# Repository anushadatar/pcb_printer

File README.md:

# Etch a Schech : CNC PCB Mill
This repository contains documentation, firmware, and software for Aiden Carley-Clopton, Quinn Kelley, Josh Deng, and Anusha Datar's Olin College Principles of Engineering FA18 final project. Over the course of three two-week sprints, we developed a highly functional and robust two-axis compound table with z-axis spindle assembly capable of milling Printed Circuit Boards (PCBs).

## Docs
The docs directory contains the source for the project [website](https://anushadatar.github.io/pcb_printer/), which includes extensive documentation of the overall project architeture, subsystem development, and the design and implementation process. It also contains a more general [poster](https://github.com/anushadatar/pcb_printer/blob/master/docs/artifacts/poster.pdf) for external documentation purposes.

## Firmware
The firmware directory contains the production source code for the real-time control system of the final project and test code associated with hardware integration and system maintenance. 

The [gcode_parse/](https://github.com/anushadatar/pcb_printer/tree/master/firmware/gcode_parse) directory contains code that, with the necessary dependencies, can be compiled for the Arduino Uno V3 and flashed onto the chip by means of the [gcode_parse.ino](https://github.com/anushadatar/pcb_printer/blob/master/firmware/gcode_parse/gcode_parse.ino) file. 

## Software
The software directory contains the software to run the high-level computation necessary to determine and send commands to the real-time controller. 

## Dependencies
The [software page of the project website](https://anushadatar.github.io/pcb_printer/software.html) contains links to all of the external software packages necessary to run this code. For more software setup details for the computational platform, use the software [guide](https://github.com/anushadatar/pcb_printer/blob/master/software/README.md). Note that a new run file with the proper pathing is necessary for any new environment, and for the code to run properly the environment must be UNIX-compliant.

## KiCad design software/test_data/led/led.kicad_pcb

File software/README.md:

This software directory's function is to develop a framework to convert a .gbr
file output into a gcode equivalent file (containing coordinates and paths) and then convert that into
paths for the CNC. Those paths can then yield motor instructions for the CNC.

The main path planning is handled by the third-party tool Flatcam. Installation can be tricky; streamlined Ubuntu instructions
are included below. Raspberry Pi setup requires additional adjustments to the Flatam stack - contact us for details!

## Linux Setup Instructions
While the Etch A Schech uses a Raspberry Pi to setup up computation and streaming, it can often be more convenient to use a machine with Linux for software and testing. To set up this framework, first install the Flatcam Dependencies:
Some of the dependencies will need to be installed separately:
 - [SIP](https://www.riverbankcomputing.com/software/sip/download)
 
Download the newest stable source .tar.gz file from [here](https://www.riverbankcomputing.com/software/sip/download). Untar it using
`tar -xvf [folderName] `. 

Then, install the package with the following commands. 
~~~~~
cd [folderName]
python3 configure.py
make
sudo make install
~~~~~
- [PyQt4](https://www.riverbankcomputing.com/software/pyqt/download)

Download the newest stable source .tar.gz file from [here](https://www.riverbankcomputing.com/software/sip/download). Untar it using
`tar -xvf [folderName] `. 

Then, install the package with the following commands. If this fails, try moving on to the next step - it may be resolved by the Flatcam setup_ubuntu shell script.
~~~~~
cd [folderName]
python3 configure.py 
make
sudo make install
~~~~~
- [Flatcam 8.5](https://bitbucket.org/jpcgt/flatcam/downloads/) 

Finally, actually install flatcam. Grab the zip file for Flatcam from [here](https://bitbucket.org/jpcgt/flatcam/downloads/).
~~~~
cd [folderName]
chmod +x setup_ubuntu.sh
sudo ./setup_ubuntu.sh
python FlatCAM.py
~~~~
A flatcam window should launch following this final command. 

Once the proper software has been installed, configure the necessary environment variables to run the bash scripts.
To do that, instantiate pointers to this software folder and to your flatcam installation by adding the following lines to your .bashrc:
~~~~
export $ETCH_SW_DIR='/PATH/TO/SW/DIR'
export $FLATCAM_DIR='/PATH/TO/FLATCAM/INSTALL'
~~~~

This system has been validated on Ubuntu 16.04, Ubuntu 18.04, and Raspbian Jessie.

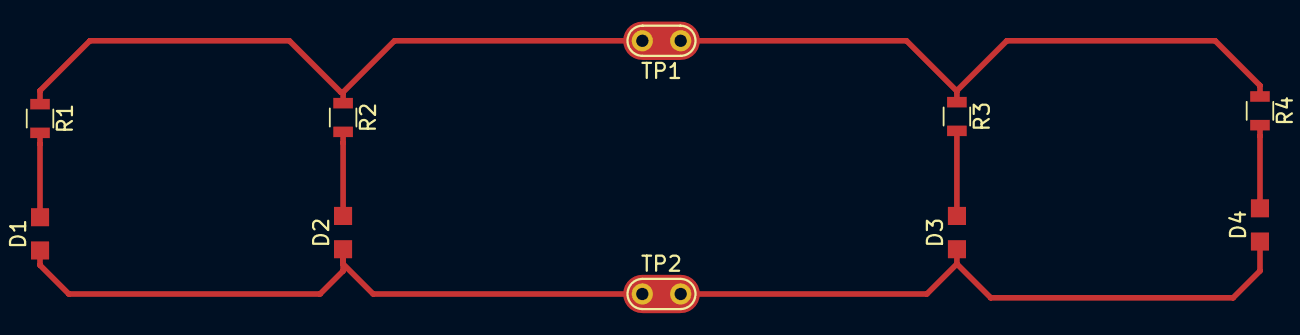
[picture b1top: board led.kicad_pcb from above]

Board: 2 copper layers, 10 parts (0 on the bottom side), 6 nets.

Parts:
D1, D2, D3, D4: LED; LED_0805_No_Silk_OEM
R1, R2, R3, R4: R; R_0805
TP1, TP2: TestPoint; Test_Point

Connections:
GND: D1.1, D2.1, D3.1, D4.1, TP2.1
unnamed: D1.2, R1.2
unnamed: D2.2, R2.2
unnamed: D3.2, R3.2
unnamed: D4.2, R4.2
unnamed: R1.1, R2.1, R3.1, R4.1, TP1.1

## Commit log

2018-10-15 add sample gerber files
2018-10-15 kicad 5 x2 example
2018-10-16 Reorg and architecture start.
2018-10-16 reorg
2018-10-17 stepper testing file and h bridge schematic project
2018-10-17 Reorganization.
2018-10-20 basic stepper functional
2018-10-23 started writing this buggy gcode parse lol
2018-10-23 more reorg
2018-10-23 add line drawing function
2018-10-23 fix stepper class motor rpm so that it compiles
2018-10-24 supposedly finished basic gcoder parse that reads XY and G
2018-10-24 Test two (2) steppers
2018-10-24 but on an arduino
2018-10-24 able to do rectangular drawing
2018-10-24 added start of arc
2018-10-24 too fast too furious
2018-10-24 basic flatcam gcode parser
2018-10-24 comment gcode_format.py
2018-10-25 x and y moves at the same time; add a space in front of gcoder formatting
2018-10-25 change cm_scaling so that the gantry thing draws circle
2018-10-26 default relative mode and remove the additional step in moving
2018-10-26 Starting cleanup
2018-10-28 Pushing raspi gcode test data.
2018-10-29 added a sample command line parser; started the streamer code; deleted serial config from format.py
2018-10-30 gcode streaming in relative x, y, z
2018-10-30 add finished gcode streamer coder; to be tested
2018-11-02 moved gcode parser
2018-11-02 added test scripts. Maybe set up an ubuntu testing environment.
2018-11-02 a script?
2018-11-04 modify gcode formatter to give the write dimension in mm and catch different combinations of X,Y,Z
2018-11-06 stepper speed to 60; encode all python streaming messages; line termination with \n and request for new line is $
2018-11-07 actually call the stream function; add dremel motor arduino code
2018-11-08 started function docs
2018-11-08 stream capability
2018-11-08 reorg for sprint 2 review prep
2018-11-08 don't run everything at once
2018-11-13 easy state machine then I guess?
2018-11-14 adding more automation stuff for raspi config.
2018-11-14 renamed one (1) folder
2018-11-14 Create CNAME
2018-11-16 started python script to generate tcl file.
2018-11-21 put up a template site, sad
2018-11-21 Create images
2018-11-21 Rename docs/README.md to docs/css/README.md
2018-11-21 starting config
2018-11-21 added more etch a schech words.
2018-11-21 removed bottom carosel and footer.
2018-11-21 added pages + nav
2018-11-22 Added page banners.
2018-11-22 added artifacts folder.
2018-11-23 Created script automation and added example stuff.
2018-11-24 Added SVG file support.
2018-11-24 Added differentiated run scripts.
2018-11-24 added the start of an explanation
2018-11-24 literally added a comment to pi_run. TODO check that it works.
2018-11-24 Update issue templates
2018-11-25 fix microstep connection error in software
2018-11-26 adding more state to allow arduino to control motor on/off
2018-11-27 updated README after setting up yet another pi
2018-11-27 click click svg
2018-11-28 decoder capability
2018-11-29 updated with encoder parsing
2018-11-29 z axis testing
2018-11-29 ino file changes.
2018-11-29 What is a GUI and who let it happen.
2018-11-29 update loaded to arduino
2018-11-29 adding doc for raspi setup things.
2018-11-29 fix z axis positioning
2018-11-29 change knob scaling factor
2018-11-29 we out here trying
2018-11-30 pcb traces
2018-11-30 added to josh's run script
2018-11-30 olin O
2018-11-30 updating with o gcode/
2018-12-01 proto board circuit
2018-12-02 update circuit to include separate power control for DC motor
2018-12-02 the whole gang's here folks
2018-12-02 we out here adding links
2018-12-02 fixed carousel
2018-12-03 update to make axis change circuit
2018-12-03 but who is quinn kelley?
2018-12-04 updated schematic with nfet driving the brushed motor
2018-12-04 we will try to drill holes
2018-12-04 jogging axes are now live
2018-12-06 Web design is my passion
2018-12-07 added placeholder images.
2018-12-07 adding circuit images
2018-12-07 Clicky photos
2018-12-07 change table name
2018-12-07 remove the black box around home
2018-12-07 adding some unformatted content to electrical, hope I didn't break anythign
2018-12-07 fixing budget site
2018-12-07 dumped some content into sprints; added unenclosed tags
2018-12-08 etch not ech
2018-12-08 L for testing
2018-12-08 ????????????? exit state.
2018-12-08 update website, add exit state for the printer
2018-12-08 gui updates. to port to pi, just change every instance of anusha to pi
2018-12-09 Pi run gui
2018-12-09 more words about power
2018-12-09 even more words
2018-12-09 Fixed some photos.
2018-12-09 please help
2018-12-09 stay centered, kids
2018-12-09 Fixed centering.
2018-12-09 final sprint...
2018-12-09 witty comments?
2018-12-09 fix wit a bit
2018-12-09 fix print 3 image naming
2018-12-10 limit switch code; update schematic; website wit fix
2018-12-10 1/123128382138
2018-12-10 new logo
2018-12-10 state machine for arduino
2018-12-10 change the scaling of electrical images from absolute to relative
2018-12-11 name tag
2018-12-11 drill
2018-12-11 kids just want to drill holes and draw pictures
2018-12-11 go away edges
2018-12-11 look at output.gcode
2018-12-11 L but larger
2018-12-11 L but positive
2018-12-11 Github messenger
2018-12-11 taking reasonably sized ls
2018-12-11 4th quadron L
2018-12-11 4th quadron l positive
2018-12-11 Please:
2018-12-11 round to 2 decimal places
2018-12-11 josh's stupidity fix
2018-12-12 write code for live z adjustment
2018-12-12 added gcode tests
2018-12-12 added mpst recent
2018-12-12 pi gui script no flash drive
2018-12-12 please work
2018-12-13 pushing for testing
2018-12-13 okay let's just ignore this
2018-12-13 stream
2018-12-13 i ate delays.
2018-12-13 asdaslkdjlsa
2018-12-13 smaller logo
2018-12-13 led output
2018-12-13 more info on the firmware stuff
2018-12-13 what worked
2018-12-13 logo update
2018-12-13 huge day to be a mechanical menu
2018-12-13 added some pages
2018-12-13 keep on pushing
2018-12-13 logo in italic
2018-12-13 added more standards and content.
2018-12-13 partial site
2018-12-13 added some to sprint pages...
2018-12-13 continued adding sprint docs..
2018-12-13 add abouts about streamer and formater
2018-12-13 Adding final zipped CAD
2018-12-13 link cad on index page
2018-12-13 clarity
2018-12-14 software adding dependencies
2018-12-14 break line
2018-12-14 HUGE gui guy
2018-12-14 Software description
2018-12-14 led doable
2018-12-14 just u wait
2018-12-14 overwriting process page
2018-12-14 Adding mechanical documentation changes
2018-12-14 we tryin
2018-12-14 Where we're going, we don't need goals.
2018-12-14 updating spindle and table pages
2018-12-14 compound table gang
2018-12-14 Updating mechanical overview page
2018-12-14 fixing navbar. not done yet.
2018-12-14 fixed navbars...
2018-12-14 all pain is temporary
2018-12-14 final additional info
2018-12-14 mid edits is not how this works but eh
2018-12-14 link the long video first
2018-12-14 fix images
2018-12-14 added interactive CAD model
2018-12-14 caption to pcb image
2018-12-14 it tkaes soem
2018-12-14 adding enclosure html
2018-12-14 fixing hero image
2018-12-14 asdadsgldsifj
2018-12-14 changing JPG to jpg
2018-12-14 sadsads
2018-12-14 the end
2018-12-14 changing file extensions for jpg to match images
2018-12-14 fix index page naming
2018-12-14 asdASd
2018-12-14 prev
2018-12-14 social media clout
2018-12-16 added poster template.
2018-12-17 the only way to leave the gantry gang is...
2018-12-17 millner
2018-12-21 Modified personal run script to clean up personal home directory.
2018-12-21 drafted top-level README
    it's never too late to document...
2018-12-24 Saturdays are fo the boys, and sundays are for new run frameworks.
2018-12-26 streaming, not screaming... i think
2018-12-31 we don't need no dependencies
